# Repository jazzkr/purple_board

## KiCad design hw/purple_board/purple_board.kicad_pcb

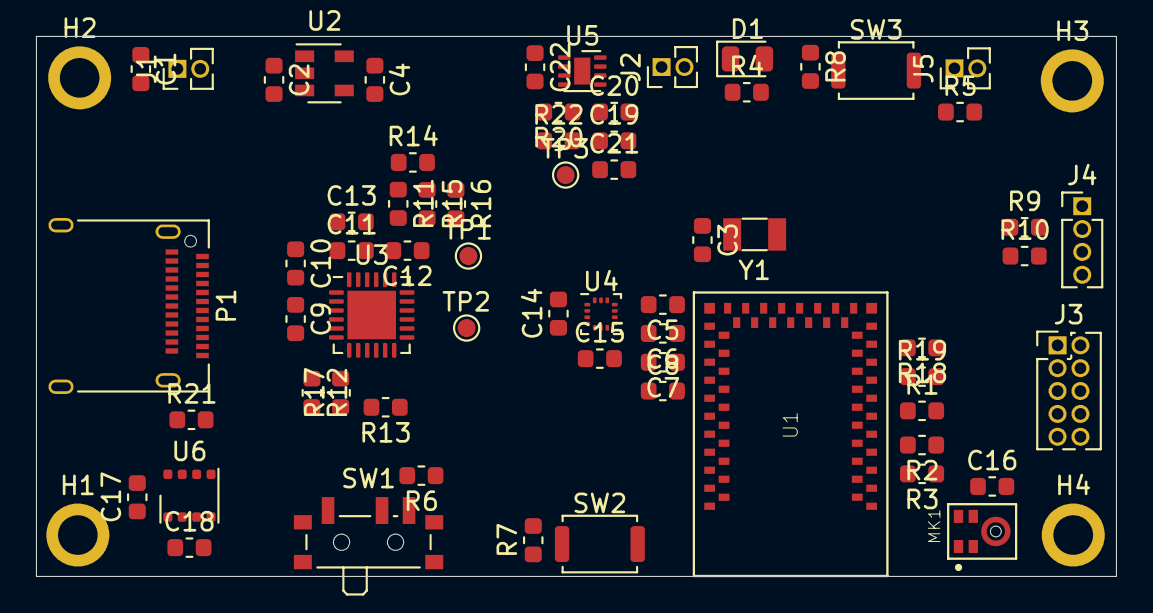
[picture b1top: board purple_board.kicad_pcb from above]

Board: 2 copper layers, 60.0 x 30.0 mm, 69 parts (0 on the bottom side), 47 nets, no tracks yet.

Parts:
C1, C6, C15: 10u; C_0603_1608Metric
C2, C4, C7, C10, C11, C12, C16: 1u; C_0603_1608Metric
C3, C5: 15p; C_0603_1608Metric
C8, C13, C14, C17, C18, C22: 100n; C_0603_1608Metric
C9: 4.7u; C_0603_1608Metric
C19: 10n; C_0603_1608Metric
C20, C21: DNP; C_0603_1608Metric
D1: LED; LED_0805_2012Metric
H1, H2, H3, H4: MountingHole_Pad; MountingHole_2.2mm_M2_ISO7380_Pad
J1: PWR_IN; PinHeader_1x02_P1.27mm_Vertical
J2: CAP_PAD; PinHeader_1x02_P1.27mm_Vertical
J3: JTAG; PinHeader_2x05_P1.27mm_Vertical
J4: LED_STRIP; PinHeader_1x04_P1.27mm_Vertical
J5: LED_PWR; PinHeader_1x02_P1.27mm_Vertical
MK1: SPH0641LM4H-1; MIC_SPH0641LM4H-1
P1: USB_C_Plug; USB_C_Receptacle_Amphenol_12401610E4-2A
R1, R2, R3, R20, R21: 10K; R_0603_1608Metric
R4: 330R; R_0603_1608Metric
R5, R6, R7, R8, R9, R10, R12, R13, R14: 100K; R_0603_1608Metric
R11, R17: 1K; R_0603_1608Metric
R15: 22K; R_0603_1608Metric
R16: 100R; R_0603_1608Metric
R18, R19, R22: 0R; R_0603_1608Metric
SW1: HOST_SW; SW_SPDT_PCM12
SW2: PAIR_BTN; SW_Push_SPST_NO_Alps_SKRK
SW3: RESET; SW_Push_SPST_NO_Alps_SKRK
TP1: POK2; TestPoint_Pad_D1.0mm
TP2: POK3; TestPoint_Pad_D1.0mm
TP3: CAP_PAD; TestPoint_Pad_D1.0mm
U1: ARTEMIS_MODULE; ARTEMIS_FP
U2: NCP718xSN330; SOT-23-5
U3: STUSB4500QTR; QFN-24-1EP_4x4mm_P0.5mm_EP2.7x2.7mm
U4: LIS2DH; LGA-14_2x2mm_P0.35mm_LayoutBorder3x4y
U5: AT42QT1011-M; DFN-8-1EP_2x2mm_P0.5mm_EP0.9x1.5mm
U6: BME680; Bosch_LGA-8_3x3mm_P0.8mm_ClockwisePinNumbering
Y1: 32.768kHz; Crystal_SMD_3215-2Pin_3.2x1.5mm

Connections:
+3V3: C4.1, C6.1, C7.1, C8.1, C14.1, C15.1, C16.1, C17.1, C18.1, C22.1, J3.1, MK1.5, R2.1, R3.1, R7.2, R8.2, R18.1, R21.2, SW1.1, U1.VDD@36, U1.VDD@37, U2.5, U4.3, U4.4, U4.7, U4.8, U5.7, U6.6, U6.8
/ACC_INT: U1.~D5, U4.6
/BOOT: R1.1, U1.BOOT
/CAP_MODE: R18.2, R19.1, U1.D7, U5.6
/CAP_PAD: J2.1, J2.2, R20.2, R22.1
/CAP_SENSE: U1.~D6, U5.5
/D23_LED: R4.1, U1.~D23
/HOST_SW: R6.1, U1.~D45
/I2C1_SCL: R2.2, U1.D8, U3.7, U4.1, U6.4
/I2C1_SDA: R3.2, U1.D9, U3.8, U4.2, U6.3
/LEDS_CLK: R9.1, U1.D0
/LEDS_DAT: R10.1, U1.D1
/LED_ON: R5.1, U1.D2
/PAIR_BTN: R7.1, SW2.1, U1.~D44
/PDM_CLK: MK1.4, U1.~AD12
/PDM_DAT: MK1.1, U1.~AD11
/RESET_N: J3.10, R8.1, SW3.1, U1.~RST
/SWDCLK: J3.4, U1.SWDCK
/SWDIO: J3.2, U1.SWDIO
/SWO: J3.6, U1.~D22
/USB_INT: U1.~D4, U3.19
/USB_RESET: R12.1, U1.D3, U3.6
/usb/CC1: P1.A5, U3.1, U3.2
/usb/CC2: P1.B5, U3.4, U3.5
GND: C1.2, C2.2, C3.2, C4.2, C5.2, C6.2, C7.2, C8.2, C9.2, C10.2, C11.2, C12.2, C14.2, C15.2, C16.2, C17.2, C18.2, C22.2, D1.1, H1.1, H2.1, H3.1, H4.1, J1.1, J3.3, J3.5, J3.9, J4.4, MK1.2, MK1.3, P1.A1, P1.A12, P1.B1, P1.B12, P1.S1, R1.2, R5.2, R12.2, R13.2, R19.2, SW1.3, SW2.2, SW3.2, U1.GND@1, U1.GND@22, U1.GND@38, U1.GND@39, U1.GND@47, U1.GND@59, U2.2, U3.10, U3.22, U3.25, U4.9, U4.10, U4.11, U4.12, U4.13, U4.14, U5.4, U5.9, U6.1, U6.5, U6.7
unnamed: C3.1, U1.XI, Y1.1
unnamed: C5.1, U1.XO, Y1.2
unnamed: C11.1, U3.23
unnamed: C12.1, U3.21
unnamed: C13.2, R16.2
unnamed: C19.1, C20.1, C21.1, R20.1, U5.1
unnamed: C19.2, C20.2, C21.2, U5.8
unnamed: D1.2, R4.2
unnamed: J4.2, R9.2
unnamed: J4.3, R10.2
unnamed: R14.2, R15.1, R16.1
unnamed: R6.2, SW1.2
unnamed: R11.2, U3.18
unnamed: R13.1, U3.12, U3.13
unnamed: R15.2, U3.16
unnamed: R17.2, U3.9
unnamed: R21.1, U6.2
unnamed: R22.2, TP3.1
unnamed: TP1.1, U3.20
unnamed: TP2.1, U3.14
VBUS: C9.1, C10.1, P1.A4, P1.A9, P1.B4, P1.B9, R11.1, R14.1, U3.24
VDC: C1.1, C2.1, C13.1, J1.2, J4.1, J5.1, R17.1, U2.1, U2.3

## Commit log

2021-01-03 Update schematics + placement, add ref and libs
2021-01-03 Fix schematic
